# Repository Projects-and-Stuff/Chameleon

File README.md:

# Chameleon #
#### A colorful RBG LED drink coaster with capacitive sensing ####

---

*File Structure*

* ./Firmware/ --> Firmware for the project (Written in C Utilizing AVR Studio 5 and AVRGCC)
* ./Hardware/ --> Kicad Project for Chameleon
* ./GerberOutput/ --> The latest Gerber Files for manufacture
* ./Notes/ --> Project Notes, BOM, and Research

---

Additional information, research, and notes can be found at http://www.projectsandstuff.com, or email us at support@projectsandstuff.com

Let us know if you fork and make improvements. We'd be glad to consider merges that improve this project.

---

Updates can be found in the Project Log, in the Notes folder

---

CURRENT AUTHORS:

> [Jack Linke](http://www.jacklinke.com)
jacklinke@gmail.com

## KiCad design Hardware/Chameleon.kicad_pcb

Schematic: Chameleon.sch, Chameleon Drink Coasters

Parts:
BEAD1: Ferrite
BT1: 3.7V 500mAh
C1, C6, C22: 10uF
C2, C3, C4, C5, C7, C16, C18, C21: 0.1uF
C8, C10, C12, C13, C15, C17: 1nF
C9: .1uF
C11: 4.7nF
C14: 10uF
C19: 47uF
C20: 1uF
CS0: 4.7nF
D1, D2, D3, D4, D5: RGB_LED
D6: LED
D7, D13: ZLLS410TA
D8, D9, D10, D11, D12: White LED
F1: PTC FUSE
IC1: ATXMEGA16A4U-A-MODIFIED; VQFN44
J1: USB-MICRO-B
L1: 10uH
L2: 33uH
P1: PDI
R1, R2, R4, R6, R7, R8, R9, R11, R13, R15, R16, R17, R18, R20, R21, R24, R25: 10k
R3, R5, R10, R12, R14: 120
R19: 4k
R22: 10k
R23: 1M
R26, R28: 100k
R27: 300k
RX0: 1k
RY0: 1k
RYB0: 470k
SW1: TL1105JAF160Q
SW2: TL1105SPF250Q
SW3: TL3315NF160Q
U2: AS1121
U3: TLV71333PDBVR; SOT-23-5
U4: NCP1402
U5: SI3588DV
XOYO1: CAPSENSOR

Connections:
/AS_MODE: IC1.29, R6.1, U2.3 (MODE)
/D+: IC1.27, J1.3 (D+)
/D-: IC1.26, J1.2 (D-)
/GSCLK: IC1.10, U2.24 (GSCLK)
/MISO: IC1.16, U2.23 (SDO)
/MODE_SELECT: C9.1, IC1.36, R22.2, SW1.2
/MOSI: IC1.15, U2.2 (SDI)
/OEN: IC1.11, R8.2, U2.31 (OEN)
/P2_EN: IC1.33, R24.1, U4.1 (CE)
/PD: IC1.32, R7.2, U2.29 (PD)
/PD0: IC1.41, R2.1
/PD1: IC1.42, R4.1
/PD2: IC1.43, R9.1
/PD3: IC1.44, R11.1
/PD4: IC1.1, R13.1
/PD5: IC1.2, R15.1
/PD6: IC1.5, R16.1
/PD7: IC1.6, R17.1
/PD8: IC1.7, R18.1
/PD9: IC1.37, R20.1
/PD10: IC1.25, R21.1
/PDI_CLK: IC1.35, P1.5, R1.2, SW3.3, SW3.4
/PDI_DATA: IC1.34, P1.1
/SCK: IC1.17, U2.1 (CLK)
/SHIELD: C11.1, J1.6 (SHELL1), J1.7 (SHELL2), J1.8 (SHELL3), J1.9 (SHELL4), R23.1
/SMP: IC1.13, RYB0.1
/VCC: C7.1, C18.1, L1.1, P1.2, R1.1, R7.1, R8.1, R22.1, U2.25 (VCC), U2.27 (VCC), U3.5 (OUT)
/VLED: C8.1, C10.1, C12.1, C13.1, C15.1, C17.1, C19.1, D1.1 (Ra), D1.3 (Ga), D1.5 (Ba), D2.1 (Ra), D2.3 (Ga), D2.5 (Ba), D3.1 (Ra), D3.3 (Ga), D3.5 (Ba), D4.1 (Ra), D4.3 (Ga), D4.5 (Ba), D5.1 (Ra), D5.3 (Ga), D5.5 (Ba), D6.1 (A), D7.2 (K), U4.2 (OUT)
/WL1: IC1.20, R3.1
/WL2: IC1.21, R5.1
/WL3: IC1.22, R10.1
/WL4: IC1.23, R12.1
/WL5: IC1.24, R14.1
/X0: IC1.12, RX0.1
/XERR: IC1.28, U2.22 (XERR)
/Y0A: CS0.1, IC1.4, RY0.1
/Y0B: CS0.2, IC1.40, RYB0.2
/~SS~: IC1.14, U2.32 (LD)
GND: BT1.1 (+), C1.2, C2.2, C3.2, C4.2, C5.2, C6.2, C7.2, C8.2, C9.2, C10.2, C11.2, C12.2, C13.2, C14.2, C15.2, C16.2, C17.2, C18.2, C19.2, D8.2 (K), D9.2 (K), D10.2 (K), D11.2 (K), D12.2 (K), IC1.3, IC1.8, IC1.18, IC1.30, IC1.38, IC1.45, J1.5 (GND), P1.6, R2.2, R4.2, R6.2, R9.2, R11.2, R13.2, R15.2, R16.2, R17.2, R18.2, R19.2, R20.2, R21.2, R23.2, R24.2, SW1.1, SW2.1, SW3.1, SW3.2, U2.30 (GND), U2.33 (GND_PAD), U3.2 (GND), U4.4 (GND), U5.6
unnamed: BEAD1.1, C1.1, C2.1, C3.1, C4.1, IC1.9, IC1.19, IC1.31, L1.2
unnamed: D5.2 (Rc), U2.20 (OUT14)
unnamed: D6.2 (K), U2.21 (OUT15)
unnamed: R19.1, U2.26 (IREF)
unnamed: D5.4 (Gc), U2.19 (OUT13)
unnamed: D1.4 (Gc), U2.5 (OUT1)
unnamed: D1.6 (Bc), U2.4 (OUT0)
unnamed: D1.2 (Rc), U2.6 (OUT2)
unnamed: D2.6 (Bc), U2.7 (OUT3)
unnamed: D2.4 (Gc), U2.8 (OUT4)
unnamed: D2.2 (Rc), U2.9 (OUT5)
unnamed: D3.6 (Bc), U2.10 (OUT6)
unnamed: D3.4 (Gc), U2.11 (OUT7)
unnamed: D3.2 (Rc), U2.14 (OUT8)
unnamed: D4.6 (Bc), U2.15 (OUT9)
unnamed: D4.4 (Gc), U2.16 (OUT10)
unnamed: D4.2 (Rc), U2.17 (OUT11)
unnamed: D5.6 (Bc), U2.18 (OUT12)
unnamed: RY0.2, XOYO1.2
unnamed: RX0.2, XOYO1.1
unnamed: D13.1 (A), R27.2, R28.1
unnamed: BT1.2 (-), C21.1, F1.2, R25.1, R26.1, U5.2
unnamed: C20.2, C21.2, R26.2, U5.3, U5.5
unnamed: C20.1, D13.2 (K), R25.2, SW2.2
unnamed: C22.2, R27.1, U5.1
unnamed: D7.1 (A), L2.2, U4.5 (LX)
unnamed: BEAD1.2, C5.1, C6.1, IC1.39
unnamed: F1.1, J1.1 (VBUS)
unnamed: D10.1 (A), R10.2
unnamed: D8.1 (A), R3.2
unnamed: D9.1 (A), R5.2
unnamed: D11.1 (A), R12.2
unnamed: D12.1 (A), R14.2
unnamed: C14.1, C16.1, C22.1, L2.1, R28.2, U3.1 (IN), U3.3 (~EN~), U5.4

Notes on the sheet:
PDI Header
Input Power & Regulation Block
Capacitive Sensor
Need to replace with water resistant right-angle push-button switches
ZX62WRD-B-5PC
Mode Select Switch
Pulls high to initially turn AS1121 off
Pulls high to initially turn outputs off
Pulls low to initially set to Grayscale mode
Reset
AVR1017 Section 3.3.3
Ferrite Bead AVR1012 Section 2.1
White LEDs (Placed between RGB LEDs)
Pull-Down Resistors
Latching Power Block From Mosaic Industries App Notes

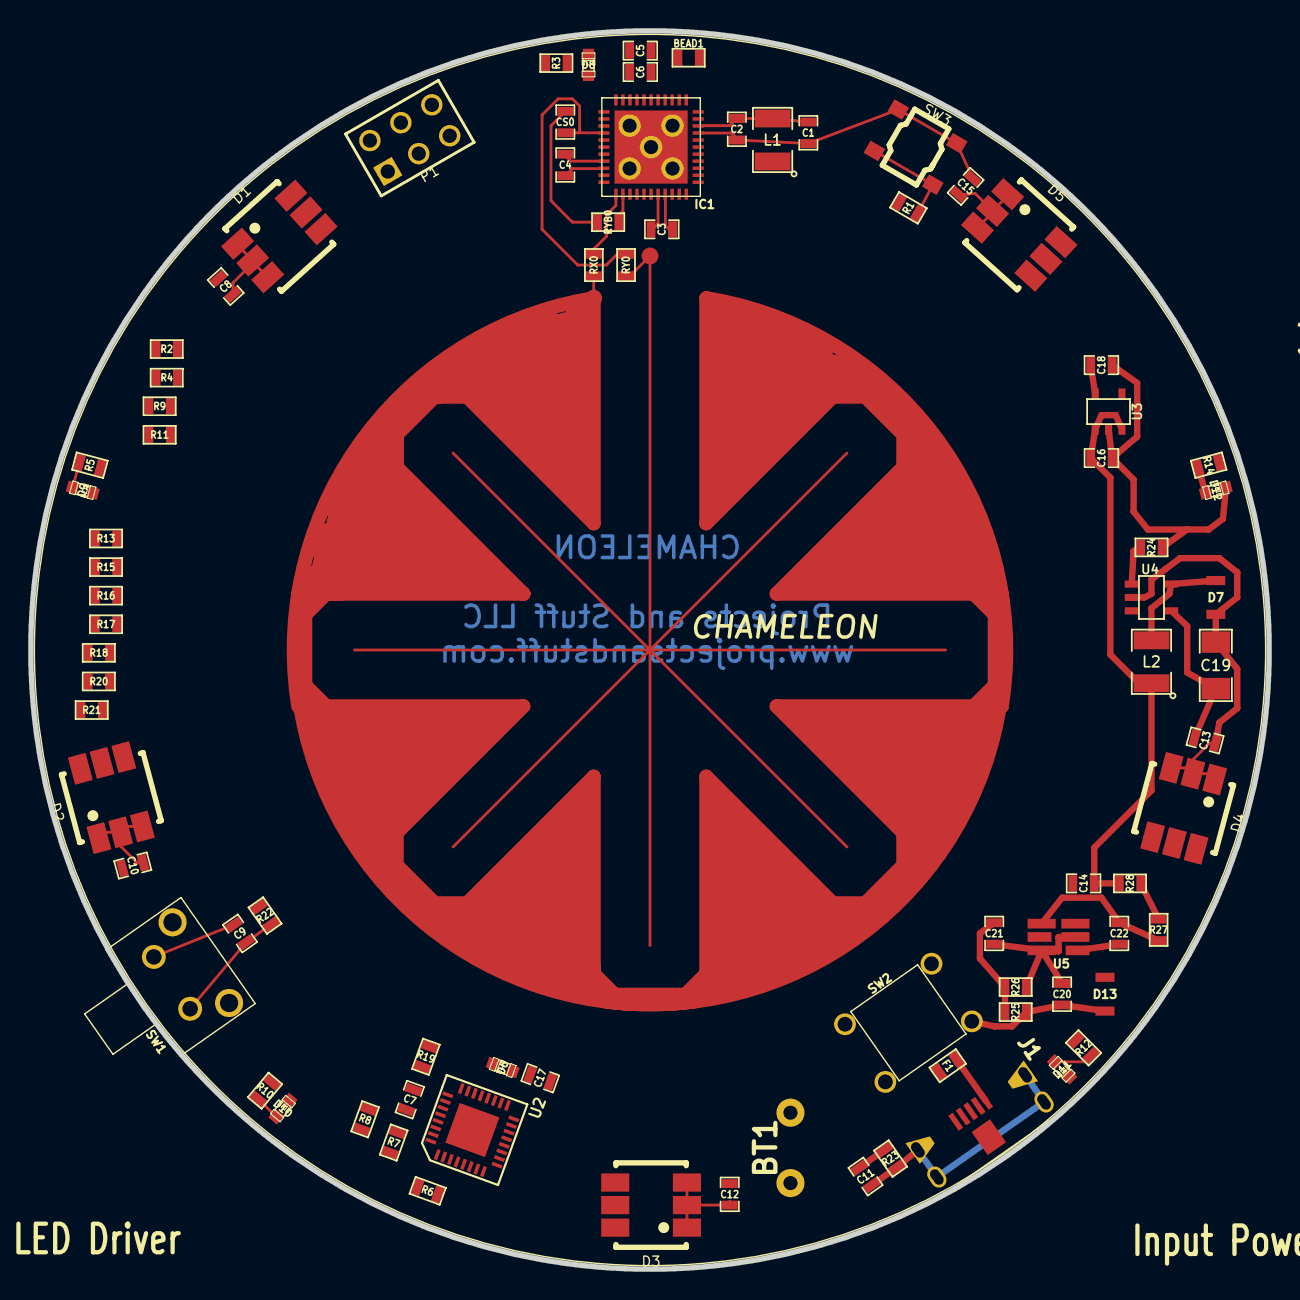
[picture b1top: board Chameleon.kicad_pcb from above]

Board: 2 copper layers, 88.0 x 88.0 mm, 83 parts (0 on the bottom side), 73 nets.

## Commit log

2012-05-06 Started initial documentation and project structure
2012-05-06 Corrected inital filenames
2012-05-06 Continued laying out schematics and updated Project Log
2012-05-06 Updated with PDF of current Schematic Image
2012-05-08 Heavily updated schematics and Project Log
2012-05-08 Added blank BOM sheet. Will update soon
2012-05-12 Made several updates to BOM, Project Log, and Schematics
2012-05-12 Updated Schematics with Boost regulator and PCA9685
2012-05-12 Updated Schematics with USB connector, and updated BOM and Project Log
2012-05-13 Annotated Schematics and finalized BOM
2012-05-13 Began working on Board design
2012-05-13 Wow, almost 4am. Worked on PCB layout. Needs more work. Components too close together
2012-05-16 Placing and routing today. Read Project Log for more detail
2012-05-16 Completed lots of placing, routing, and autorouting. Also updated Project Log
2012-05-16 Removed outdated PDF Files. Last commit before Back Importing Spectra Session File
2012-05-17 Completed Prototype design. Exported Gerbers.
2012-05-17 Updated BOM with additional sheet for non-electronic parts
2012-05-19 Added initial firmware skeleton
2012-05-20 Slight updates to Project Log
2012-06-07 Updated Project Log with notes on initial prototype
2012-06-12 Made several updates to Project Log
2012-07-03 Updated Project Log - minor
2012-08-06 Updated Project Log and initial working code for LEDs
2012-08-13 Corrected the majority of known issues in Schematics and PCB, and updated BOM and Project Log
2012-08-14 Successful Touch Sense test. Updated Firmware and Project Log
2012-08-16 Updated BOM, renamed CS1 to C14, Improved firmware slightly
2012-08-26 Cleaned up schematics and added footprint column to BOM. Yet to be populated
2012-08-28 Added I2C series resistors, updated Project Log, added PDF version of Project Log
2012-08-28 Added series resistors to the PCB
2012-09-10 Updated schematics and Project Log with new resistor values, and added PDF BOM
2012-12-21 Added basic case prototype
2012-12-21 Updated prototype case to better fit wiring and protect battery
2012-12-31 Created a basic case for the project. Not quite perfect yet.
2012-12-31 Routed board (with LEDs corrected) and updated Project Log
2012-12-31 Including Gerber and drill files.
2013-09-29 Began transitioning to updated Parts to improve function and increase capability.
2013-09-29 Made a number of notes in the schematics based on new knowledge and past mistakes.
2013-09-30 Made major updates to power management and control
2013-09-30 Updated version number
2013-09-30 Updated schematic PDF
2013-09-30 Updated PDI Header and Reset circuitry
2013-10-01 Began updating BOM with new parts and updated data.
2013-10-01 Added better USB Micro Jack
2013-10-01 Added input power to uC, modified pins, added white LEDs and SPST switch, and made other small changes.
2013-10-02 Updated BOM with current prices and mostly 0603 packages for discrete components.
2013-10-04 Finalized (for now) the schematics and annotated components.
2013-10-04 Updated Netlist
2013-10-04 Associated Components
2013-10-04 Began placing components onto board
2013-10-04 Including forgotten PCB files
2013-10-05 Added latching power block
2013-10-06 Updated schematics with annotation
2013-10-06 Created netlist and imported components into PCB
2013-10-06 Updated BOM with latching power components
2013-10-20 Began grouping components
2013-11-08 Added VQFN44 and updated XMega chip in PCB
2013-11-09 Updated XMega with Ground pin and placed several main components
2013-11-11 Placed all components, made important routes, and set keepouts for initial autoroute test run.
2013-11-11 After initial Autoroute attempt, made adjustments to component layout. Iterating again...
